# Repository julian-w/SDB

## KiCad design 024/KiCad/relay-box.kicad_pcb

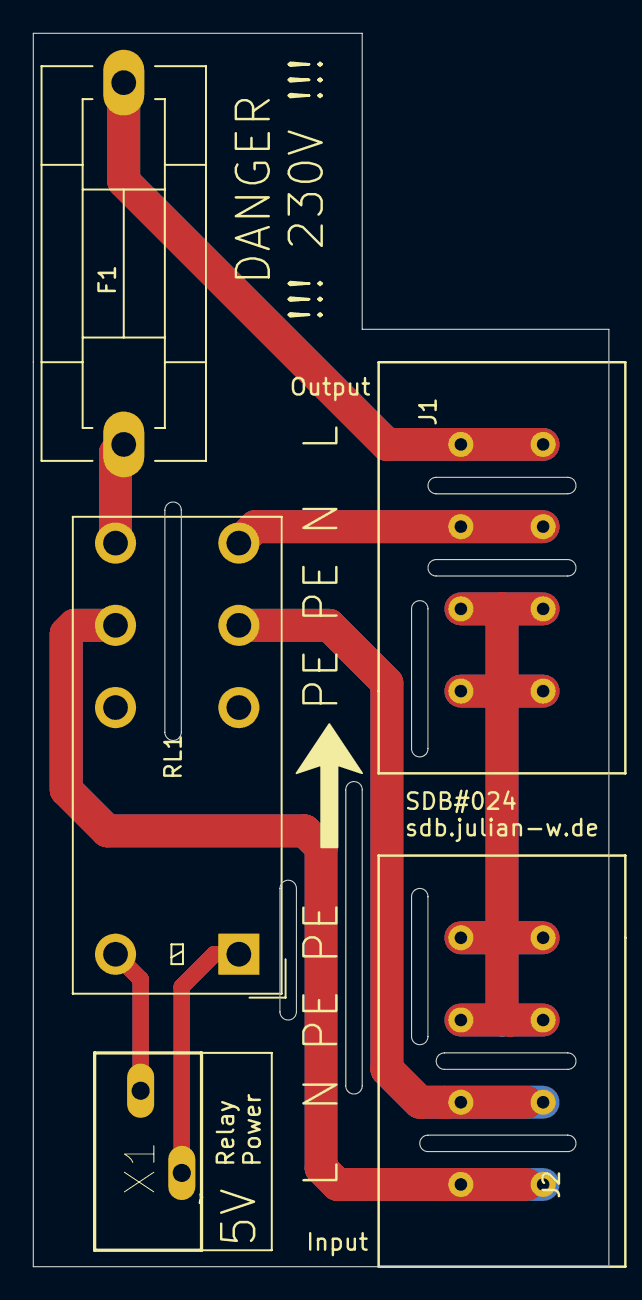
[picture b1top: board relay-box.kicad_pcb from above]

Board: 2 copper layers, 35.0 x 75.0 mm, 5 parts (0 on the bottom side), 8 nets.

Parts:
F1: Fuse; Fuseholder5x20_horiz_SemiClosed_Casing10x25mm
J1, J2: Conn_02x04_Row_Letter_Last; 5.00mm-4x2
RL1: G2RL-2-ASI-DC5; Relay_DPDT_Omron_G2RL
X1: 250-402_000-012; P-250-402

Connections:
unnamed: F1.1, RL1.5
unnamed: F1.2, J1.1a, J1.1b
unnamed: J1.2a, J1.2b, RL1.4
unnamed: J1.3a, J1.3b, J1.4a, J1.4b, J2.3a, J2.3b, J2.4a, J2.4b
unnamed: J2.1a, J2.1b, RL1.6
unnamed: J2.2a, J2.2b, RL1.3
unnamed: RL1.1, X1.L1
unnamed: RL1.8, X1.L2

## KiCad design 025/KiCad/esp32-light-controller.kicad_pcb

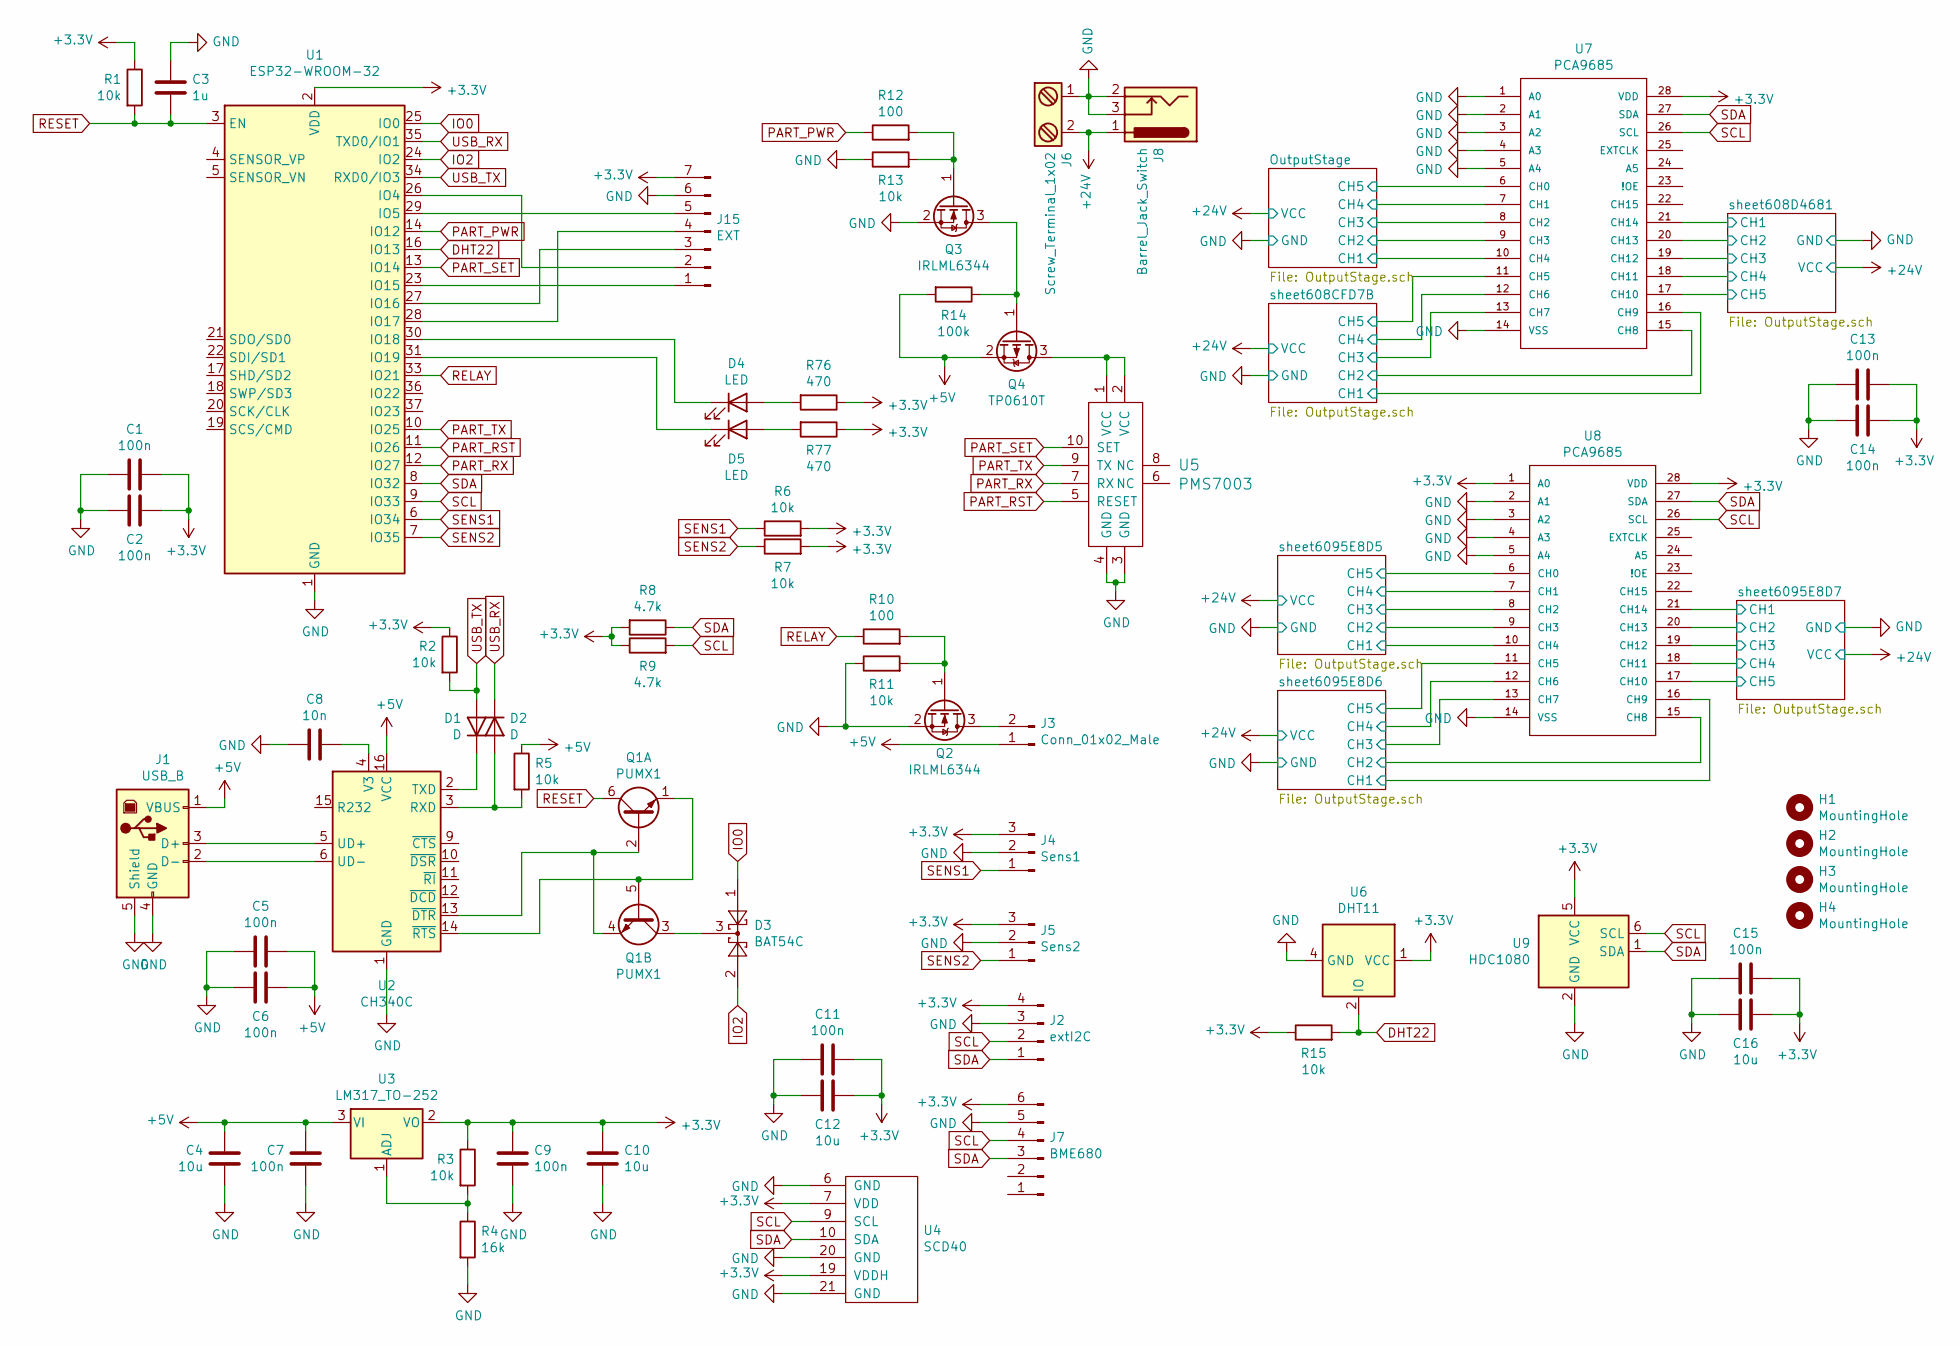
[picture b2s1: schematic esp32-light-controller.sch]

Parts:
C1, C2, C5, C6, C7, C9, C11, C13, C14, C15: 100n; C_0603
C3: 1u; C_0603
C4, C10, C12, C16: 10u; C_0603
C8: 10n; C_0603
D1, D2: D; D_SOD-123; LCSC C8598
D3: BAT54C; SOT-23
D4, D5: LED; LED_0603
H1, H2, H3, H4: MountingHole; MountingHole_3.2mm_M3
J1: USB_B; USB_B_Lumberg_2411_02_Horizontal
J2: extI2C; PinHeader_1x04_P2.54mm_Vertical
J3: Conn_01x02_Male; PinHeader_1x02_P2.54mm_Vertical
J4: Sens1; PinHeader_1x03_P2.54mm_Vertical
J5: Sens2; PinHeader_1x03_P2.54mm_Vertical
J6: Screw_Terminal_1x02; TE_826576-2_1x02_P3.96mm_Vertical
J7: BME680; PinHeader_1x06_P2.54mm_Vertical
J8: Barrel_Jack_Switch; BarrelJack_Horizontal
J15: EXT; PinHeader_1x07_P2.54mm_Vertical
Q1: PUMX1; SOT-363_SC-70-6
Q2, Q3: IRLML6344; SOT-23; LCSC C53550
Q4: TP0610T; SOT-23
R1, R2, R3, R5, R6, R7, R11, R13, R15: 10k; R_0603
R4: 16k; R_0603
R8, R9: 4.7k; R_0603
R10, R12: 100; R_0603
R14: 100k; R_0603
R76, R77: 470; R_0603
U1: ESP32-WROOM-32
U2: CH340C; SOIC-16_3.9x9.9mm_P1.27mm; LCSC C14267
U3: LM317_TO-252; TO-252-2; LCSC C75510
U4: SCD40; QFN-20_EP_10.1x10.1_Pitch1.25mm
U5: PMS7003
U6: DHT11; Aosong_DHT11_5.5x12.0_P2.54mm
U7, U8: PCA9685; SSOP-28_5.3x10.2mm_P0.65mm
U9: HDC1080; Texas_PWSON-N6; LCSC C82227

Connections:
+3V3: C1.1, C2.1, C9.1, C10.1, C11.1, C12.1, C13.1, C14.1, C15.1, C16.1, J2.4, J4.3, J5.3, J7.6, J15.7, R1.1, R2.1, R3.1, R6.2, R7.2, R8.2, R9.1, R15.1, R76.1, R77.1, U1.2 (VDD), U3.2 (VO), U4.7 (VDD), U4.19 (VDDH), U6.1 (VCC), U7.28 (VDD), U8.1 (A0), U8.28 (VDD), U9.5 (VCC)
+5V: C4.1, C5.1, C6.1, C7.1, J1.1 (VBUS), J3.1, Q4.2 (S), R5.1, R14.2, U2.16 (VCC), U3.3 (VI)
+24V: J6.2, J8.1; also elsewhere on the board
/OutputStage/CH1: U7.10 (CH4); also elsewhere on the board
/OutputStage/CH2: U7.9 (CH3); also elsewhere on the board
/OutputStage/CH3: U7.8 (CH2); also elsewhere on the board
/OutputStage/CH4: U7.7 (CH1); also elsewhere on the board
/OutputStage/CH5: U7.6 (CH0); also elsewhere on the board
/sheet608CFD7B/CH1: U7.16 (CH9); also elsewhere on the board
/sheet608CFD7B/CH2: U7.15 (CH8); also elsewhere on the board
/sheet608CFD7B/CH3: U7.13 (CH7); also elsewhere on the board
/sheet608CFD7B/CH4: U7.12 (CH6); also elsewhere on the board
/sheet608CFD7B/CH5: U7.11 (CH5); also elsewhere on the board
/sheet608D4681/CH1: U7.21 (CH14); also elsewhere on the board
/sheet608D4681/CH2: U7.20 (CH13); also elsewhere on the board
/sheet608D4681/CH3: U7.19 (CH12); also elsewhere on the board
/sheet608D4681/CH4: U7.18 (CH11); also elsewhere on the board
/sheet608D4681/CH5: U7.17 (CH10); also elsewhere on the board
/sheet6095E8D5/CH1: U8.10 (CH4); also elsewhere on the board
/sheet6095E8D5/CH2: U8.9 (CH3); also elsewhere on the board
/sheet6095E8D5/CH3: U8.8 (CH2); also elsewhere on the board
/sheet6095E8D5/CH4: U8.7 (CH1); also elsewhere on the board
/sheet6095E8D5/CH5: U8.6 (CH0); also elsewhere on the board
/sheet6095E8D6/CH1: U8.16 (CH9); also elsewhere on the board
/sheet6095E8D6/CH2: U8.15 (CH8); also elsewhere on the board
/sheet6095E8D6/CH3: U8.13 (CH7); also elsewhere on the board
/sheet6095E8D6/CH4: U8.12 (CH6); also elsewhere on the board
/sheet6095E8D6/CH5: U8.11 (CH5); also elsewhere on the board
/sheet6095E8D7/CH1: U8.21 (CH14); also elsewhere on the board
/sheet6095E8D7/CH2: U8.20 (CH13); also elsewhere on the board
/sheet6095E8D7/CH3: U8.19 (CH12); also elsewhere on the board
/sheet6095E8D7/CH4: U8.18 (CH11); also elsewhere on the board
/sheet6095E8D7/CH5: U8.17 (CH10); also elsewhere on the board
DHT22: R15.2, U1.16 (IO13), U6.2 (IO)
GND: C1.2, C2.2, C3.2, C4.2, C5.2, C6.2, C7.2, C8.2, C9.2, C10.2, C11.2, C12.2, C13.2, C14.2, C15.2, C16.2, J1.4 (GND), J1.5 (Shield), J2.3, J4.2, J5.2, J6.1, J7.5, J8.2, J8.3, J15.6, Q2.2 (S), Q3.2 (S), R4.2, R11.1, R13.1, U1.1 (GND), U1.15 (GND), U1.38 (GND), U1.39 (GND), U2.1 (GND), U4.6 (GND), U4.20 (GND), U4.21 (GND), U5.3 (GND), U5.4 (GND), U6.4 (GND), U7.1 (A0), U7.2 (A1), U7.3 (A2), U7.4 (A3), U7.5 (A4), U7.14 (VSS), U8.2 (A1), U8.3 (A2), U8.4 (A3), U8.5 (A4), U8.14 (VSS), U9.2 (GND); also elsewhere on the board
IO0: D3.1, U1.25 (IO0)
IO2: D3.2, U1.24 (IO2)
unnamed: C8.1, U2.4 (V3)
unnamed: D1.1 (K), U2.2 (TXD)
unnamed: D2.2 (A), R5.2, U2.3 (RXD)
unnamed: D3.3, Q1.3 (C2)
unnamed: D4.1 (K), U1.30 (IO18)
unnamed: D4.2 (A), R76.2
unnamed: D5.1 (K), U1.31 (IO19)
unnamed: D5.2 (A), R77.2
unnamed: J1.2 (D-), U2.6 (UD-)
unnamed: J1.3 (D+), U2.5 (UD+)
unnamed: J3.2, Q2.3 (D)
unnamed: J15.1, U1.23 (IO15)
unnamed: J15.2, U1.26 (IO4)
unnamed: J15.3, U1.27 (IO16)
unnamed: J15.4, U1.28 (IO17)
unnamed: J15.5, U1.29 (IO5)
unnamed: Q1.1 (E1), Q1.5 (B2), U2.14 (~RTS)
unnamed: Q1.2 (B1), Q1.4 (E2), U2.13 (~DTR)
unnamed: Q2.1 (G), R10.2, R11.2
unnamed: Q3.1 (G), R12.2, R13.2
unnamed: Q3.3 (D), Q4.1 (G), R14.1
unnamed: Q4.3 (D), U5.1 (VCC), U5.2 (VCC)
unnamed: R3.2, R4.1, U3.1 (ADJ)
PART_PWR: R12.1, U1.14 (IO12)
PART_RST: U1.11 (IO26), U5.5 (RESET)
PART_RX: U1.12 (IO27), U5.7 (RX)
PART_SET: U1.13 (IO14), U5.10 (SET)
PART_TX: U1.10 (IO25), U5.9 (TX)
RELAY: R10.1, U1.33 (IO21)
RESET: C3.1, Q1.6 (C1), R1.2, U1.3 (EN)
SCL: J2.2, J7.4, R9.2, U1.9 (IO33), U4.9 (SCL), U7.26 (SCL), U8.26 (SCL), U9.6 (SCL)
SDA: J2.1, J7.3, R8.1, U1.8 (IO32), U4.10 (SDA), U7.27 (SDA), U8.27 (SDA), U9.1 (SDA)
SENS1: J4.1, R6.1, U1.6 (IO34)
SENS2: J5.1, R7.1, U1.7 (IO35)
USB_RX: D2.1 (K), U1.35 (TXD0/IO1)
USB_TX: D1.2 (A), R2.2, U1.34 (RXD0/IO3)

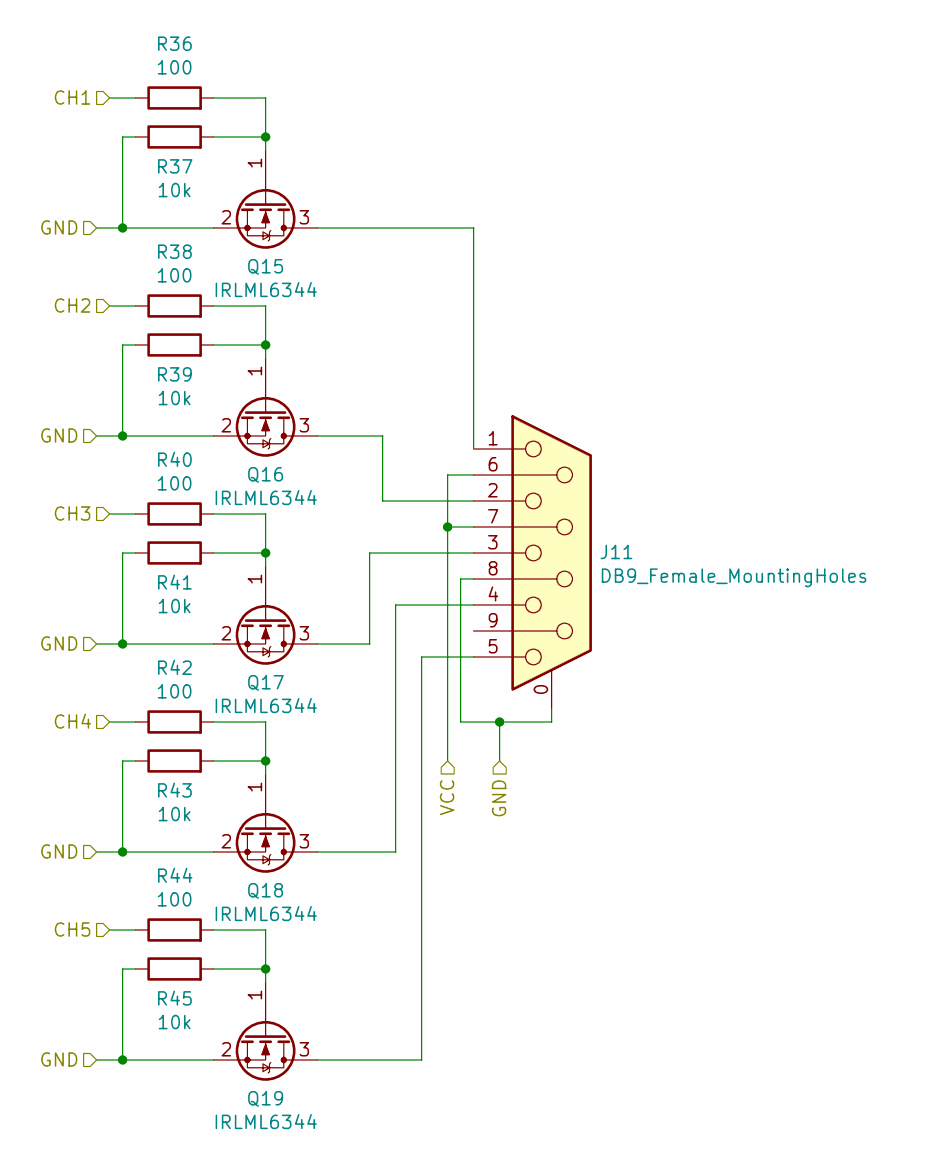
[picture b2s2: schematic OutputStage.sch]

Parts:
J9: DB9_Female_MountingHoles; DSUB-9_Female_Vertical_P2.77x2.84mm_MountingHoles; LCSC C86572
Q5, Q6, Q7, Q8, Q9: IRLML6344; SOT-23; LCSC C53550
R16, R18, R20, R22, R24: 100; R_0603
R17, R19, R21, R23, R25: 10k; R_0603

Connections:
+24V: J9.6, J9.7; also elsewhere on the board
/OutputStage/CH1: R16.1; also elsewhere on the board
/OutputStage/CH2: R18.1; also elsewhere on the board
/OutputStage/CH3: R20.1; also elsewhere on the board
/OutputStage/CH4: R22.1; also elsewhere on the board
/OutputStage/CH5: R24.1; also elsewhere on the board
GND: J9.0 (PAD), J9.8, Q5.2 (S), Q6.2 (S), Q7.2 (S), Q8.2 (S), Q9.2 (S), R17.1, R19.1, R21.1, R23.1, R25.1; also elsewhere on the board
unnamed: J9.1, Q5.3 (D)
unnamed: J9.2, Q6.3 (D)
unnamed: J9.3, Q7.3 (D)
unnamed: J9.4, Q8.3 (D)
unnamed: J9.5, Q9.3 (D)
unnamed: Q5.1 (G), R16.2, R17.2
unnamed: Q6.1 (G), R18.2, R19.2
unnamed: Q7.1 (G), R20.2, R21.2
unnamed: Q8.1 (G), R22.2, R23.2
unnamed: Q9.1 (G), R24.2, R25.2

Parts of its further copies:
J10, J11, J12, J13, J14: DB9_Female_MountingHoles; DSUB-9_Female_Vertical_P2.77x2.84mm_MountingHoles; LCSC C86572
Q10, Q11, Q12, Q13, Q14, Q15, Q16, Q17, Q18, Q19, Q20, Q21, Q22, Q23, Q24, Q25, Q26, Q27, Q28, Q29, Q30, Q31, Q32, Q33, Q34: IRLML6344; SOT-23; LCSC C53550
R26, R28, R30, R32, R34, R36, R38, R40, R42, R44, R46, R48, R50, R52, R54, R56, R58, R60, R62, R64, R66, R68, R70, R72, R74: 100; R_0603
R27, R29, R31, R33, R35, R37, R39, R41, R43, R45, R47, R49, R51, R53, R55, R57, R59, R61, R63, R65, R67, R69, R71, R73, R75: 10k; R_0603

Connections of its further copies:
+24V: J10.6, J10.7, J11.6, J11.7, J12.6, J12.7, J13.6, J13.7, J14.6, J14.7; also elsewhere on the board
/sheet608CFD7B/CH1: R26.1; also elsewhere on the board
/sheet608CFD7B/CH2: R28.1; also elsewhere on the board
/sheet608CFD7B/CH3: R30.1; also elsewhere on the board
/sheet608CFD7B/CH4: R32.1; also elsewhere on the board
/sheet608CFD7B/CH5: R34.1; also elsewhere on the board
/sheet608D4681/CH1: R36.1; also elsewhere on the board
/sheet608D4681/CH2: R38.1; also elsewhere on the board
/sheet608D4681/CH3: R40.1; also elsewhere on the board
/sheet608D4681/CH4: R42.1; also elsewhere on the board
/sheet608D4681/CH5: R44.1; also elsewhere on the board
/sheet6095E8D5/CH1: R46.1; also elsewhere on the board
/sheet6095E8D5/CH2: R48.1; also elsewhere on the board
/sheet6095E8D5/CH3: R50.1; also elsewhere on the board
/sheet6095E8D5/CH4: R52.1; also elsewhere on the board
/sheet6095E8D5/CH5: R54.1; also elsewhere on the board
/sheet6095E8D6/CH1: R56.1; also elsewhere on the board
/sheet6095E8D6/CH2: R58.1; also elsewhere on the board
/sheet6095E8D6/CH3: R60.1; also elsewhere on the board
/sheet6095E8D6/CH4: R62.1; also elsewhere on the board
/sheet6095E8D6/CH5: R64.1; also elsewhere on the board
/sheet6095E8D7/CH1: R66.1; also elsewhere on the board
/sheet6095E8D7/CH2: R68.1; also elsewhere on the board
/sheet6095E8D7/CH3: R70.1; also elsewhere on the board
/sheet6095E8D7/CH4: R72.1; also elsewhere on the board
/sheet6095E8D7/CH5: R74.1; also elsewhere on the board
GND: J10.0 (PAD), J10.8, J11.0 (PAD), J11.8, J12.0 (PAD), J12.8, J13.0 (PAD), J13.8, J14.0 (PAD), J14.8, Q10.2 (S), Q11.2 (S), Q12.2 (S), Q13.2 (S), Q14.2 (S), Q15.2 (S), Q16.2 (S), Q17.2 (S), Q18.2 (S), Q19.2 (S), Q20.2 (S), Q21.2 (S), Q22.2 (S), Q23.2 (S), Q24.2 (S), Q25.2 (S), Q26.2 (S), Q27.2 (S), Q28.2 (S), Q29.2 (S), Q30.2 (S), Q31.2 (S), Q32.2 (S), Q33.2 (S), Q34.2 (S), R27.1, R29.1, R31.1, R33.1, R35.1, R37.1, R39.1, R41.1, R43.1, R45.1, R47.1, R49.1, R51.1, R53.1, R55.1, R57.1, R59.1, R61.1, R63.1, R65.1, R67.1, R69.1, R71.1, R73.1, R75.1; also elsewhere on the board
unnamed: J10.1, Q10.3 (D)
unnamed: J10.2, Q11.3 (D)
unnamed: J10.3, Q12.3 (D)
unnamed: J10.4, Q13.3 (D)
unnamed: J10.5, Q14.3 (D)
unnamed: J11.1, Q15.3 (D)
unnamed: J11.2, Q16.3 (D)
unnamed: J11.3, Q17.3 (D)
unnamed: J11.4, Q18.3 (D)
unnamed: J11.5, Q19.3 (D)
unnamed: J12.1, Q20.3 (D)
unnamed: J12.2, Q21.3 (D)
unnamed: J12.3, Q22.3 (D)
unnamed: J12.4, Q23.3 (D)
unnamed: J12.5, Q24.3 (D)
unnamed: J13.1, Q25.3 (D)
unnamed: J13.2, Q26.3 (D)
unnamed: J13.3, Q27.3 (D)
unnamed: J13.4, Q28.3 (D)
unnamed: J13.5, Q29.3 (D)
unnamed: J14.1, Q30.3 (D)
unnamed: J14.2, Q31.3 (D)
unnamed: J14.3, Q32.3 (D)
unnamed: J14.4, Q33.3 (D)
unnamed: J14.5, Q34.3 (D)
unnamed: Q10.1 (G), R26.2, R27.2
unnamed: Q11.1 (G), R28.2, R29.2
unnamed: Q12.1 (G), R30.2, R31.2
unnamed: Q13.1 (G), R32.2, R33.2
unnamed: Q14.1 (G), R34.2, R35.2
unnamed: Q15.1 (G), R36.2, R37.2
unnamed: Q16.1 (G), R38.2, R39.2
unnamed: Q17.1 (G), R40.2, R41.2
unnamed: Q18.1 (G), R42.2, R43.2
unnamed: Q19.1 (G), R44.2, R45.2
unnamed: Q20.1 (G), R46.2, R47.2
unnamed: Q21.1 (G), R48.2, R49.2
unnamed: Q22.1 (G), R50.2, R51.2
unnamed: Q23.1 (G), R52.2, R53.2
unnamed: Q24.1 (G), R54.2, R55.2
unnamed: Q25.1 (G), R56.2, R57.2
unnamed: Q26.1 (G), R58.2, R59.2
unnamed: Q27.1 (G), R60.2, R61.2
unnamed: Q28.1 (G), R62.2, R63.2
unnamed: Q29.1 (G), R64.2, R65.2
unnamed: Q30.1 (G), R66.2, R67.2
unnamed: Q31.1 (G), R68.2, R69.2
unnamed: Q32.1 (G), R70.2, R71.2
unnamed: Q33.1 (G), R72.2, R73.2
unnamed: Q34.1 (G), R74.2, R75.2

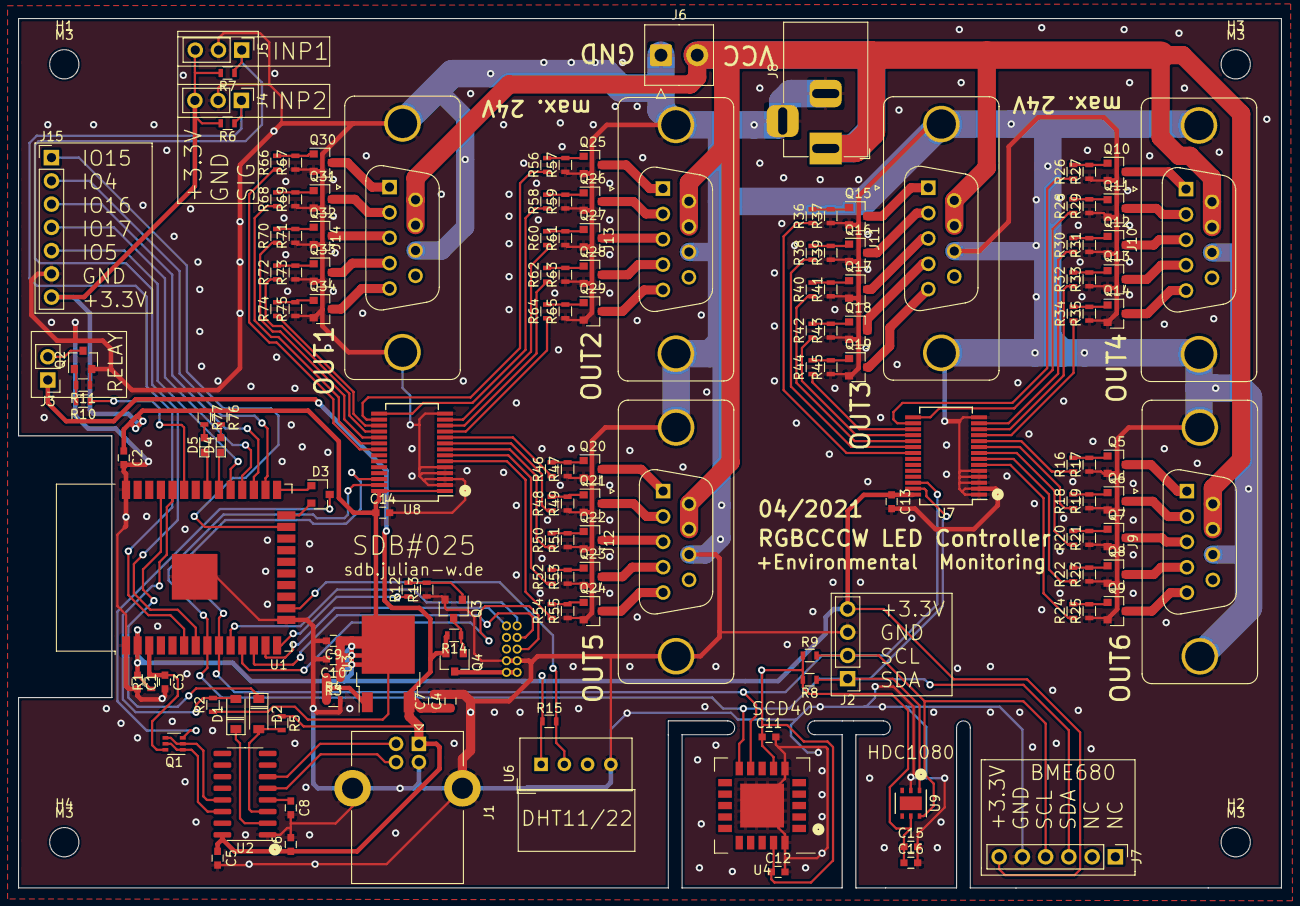
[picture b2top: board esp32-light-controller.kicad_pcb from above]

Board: 2 copper layers, 138.0 x 95.0 mm, 160 parts (1 on the bottom side), 133 nets.

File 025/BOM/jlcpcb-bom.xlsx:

Column1 | Column2 | Column3 | Column4
Comment | Designator | Footprint | LCSC
100n | C1,C2,C5,C6,C7,C9,C11,C13,C14,C15 | Capacitors_SMD:C_0603 | C14663
10u | C4,C10,C12,C16 | Capacitors_SMD:C_0603 | C19702
1u | C3 | Capacitors_SMD:C_0603 | C15849
10n | C8 | Capacitors_SMD:C_0603 | C57112
D | D1,D2 | Diodes_SMD:D_SOD-123 | C8598
BAT54C | D3 | Package_TO_SOT_SMD:SOT-23 | C14308
LED | D4 | LEDs:LED_0603 | C72043
LED | D5 | LEDs:LED_0603 | C72038
MountingHole | H1,H2,H3,H4 | Mounting_Holes:MountingHole_3.2mm_M3
USB_B | J1 | Connector_USB:USB_B_Lumberg_2411_02_Horizontal
EXT | J15 | Connector_PinHeader_2.54mm:PinHeader_1x07_P2.54mm_Vertical
extI2C | J2 | Connector_PinHeader_2.54mm:PinHeader_1x04_P2.54mm_Vertical
Conn_01x02_Male | J3 | Connector_PinHeader_2.54mm:PinHeader_1x02_P2.54mm_Vertical
Sens1 | J4 | Connector_PinHeader_2.54mm:PinHeader_1x03_P2.54mm_Vertical
Sens2 | J5 | Connector_PinHeader_2.54mm:PinHeader_1x03_P2.54mm_Vertical
Screw_Terminal_1x02 | J6 | Connector_TE-Connectivity:TE_826576-2_1x02_P3.96mm_Vertical
BME680 | J7 | Connector_PinHeader_2.54mm:PinHeader_1x06_P2.54mm_Vertical
Barrel_Jack_Switch | J8 | Connector_BarrelJack:BarrelJack_Horizontal
DB9_Female_MountingHoles | J9,J10,J11,J12,J13,J14 | Connector_Dsub:DSUB-9_Female_Vertical_P2.77x2.84mm_MountingHoles | C86572
PUMX1 | Q1 | Package_TO_SOT_SMD:SOT-363_SC-70-6 | C79972
IRLML6344 | Q2,Q3,Q5,Q6,Q7,Q8,Q9,Q10,Q11,Q12,Q13,Q14,Q15,Q16,Q17,Q18,Q19,Q20,Q21,Q22,Q23,Q2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 | Package_TO_SOT_SMD:SOT-23 | C53550
TP0610T | Q4 | Package_TO_SOT_SMD:SOT-23 | C10487
100 | R10,R12,R16,R18,R20,R22,R24,R26,R28,R30,R32,R34,R36,R38,R40,R42,R44,R46,R48,R50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 | Resistors_SMD:R_0603 | C22775
100k | R14 | Resistors_SMD:R_0603 | C25803
10k | R1,R2,R3,R5,R6,R7,R11,R13,R15,R17,R19,R21,R23,R25,R27,R29,R31,R33,R35,R37,R39,R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 | Resistors_SMD:R_0603 | C25804
16k | R4 | Resistors_SMD:R_0603 | C22818
470 | R76,R77 | Resistors_SMD:R_0603 | C23179
4.7k | R8,R9 | Resistors_SMD:R_0603 | C23162
ESP32-WROOM-32 | U1 | RF_Module:ESP32-WROOM-32 | C473012
CH340C | U2 | Package_SO:SOIC-16_3.9x9.9mm_P1.27mm | C14267
LM317_TO-252 | U3 | Package_TO_SOT_SMD:TO-252-2 | C75510
SCD40 | U4 | 009162006301150:QFN-20_EP_10.1x10.1_Pitch1.25mm
PMS7003 | U5 | Sensors_Detectors:PMS7003
DHT11 | U6 | Sensor:Aosong_DHT11_5.5x12.0_P2.54mm
PCA9685 | U7,U8 | Package_SO:SSOP-28_5.3x10.2mm_P0.65mm | C92206
HDC1080 | U9 | Package_SON:Texas_PWSON-N6 | C82227

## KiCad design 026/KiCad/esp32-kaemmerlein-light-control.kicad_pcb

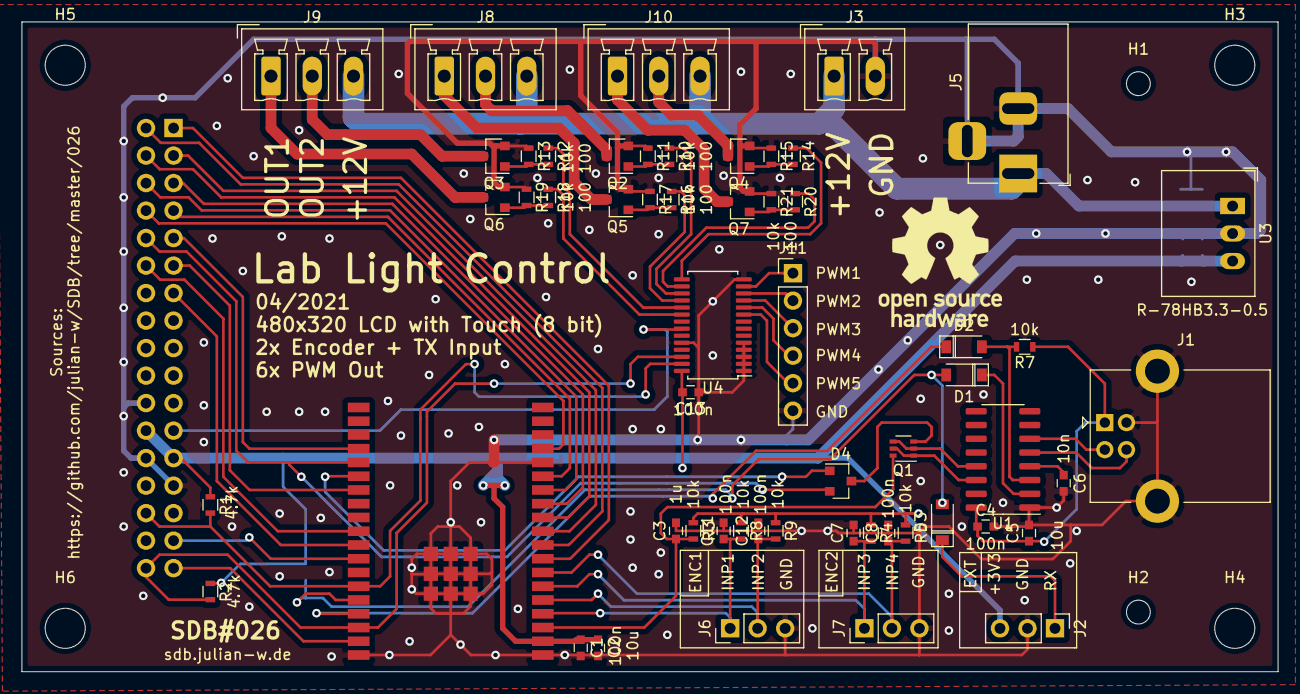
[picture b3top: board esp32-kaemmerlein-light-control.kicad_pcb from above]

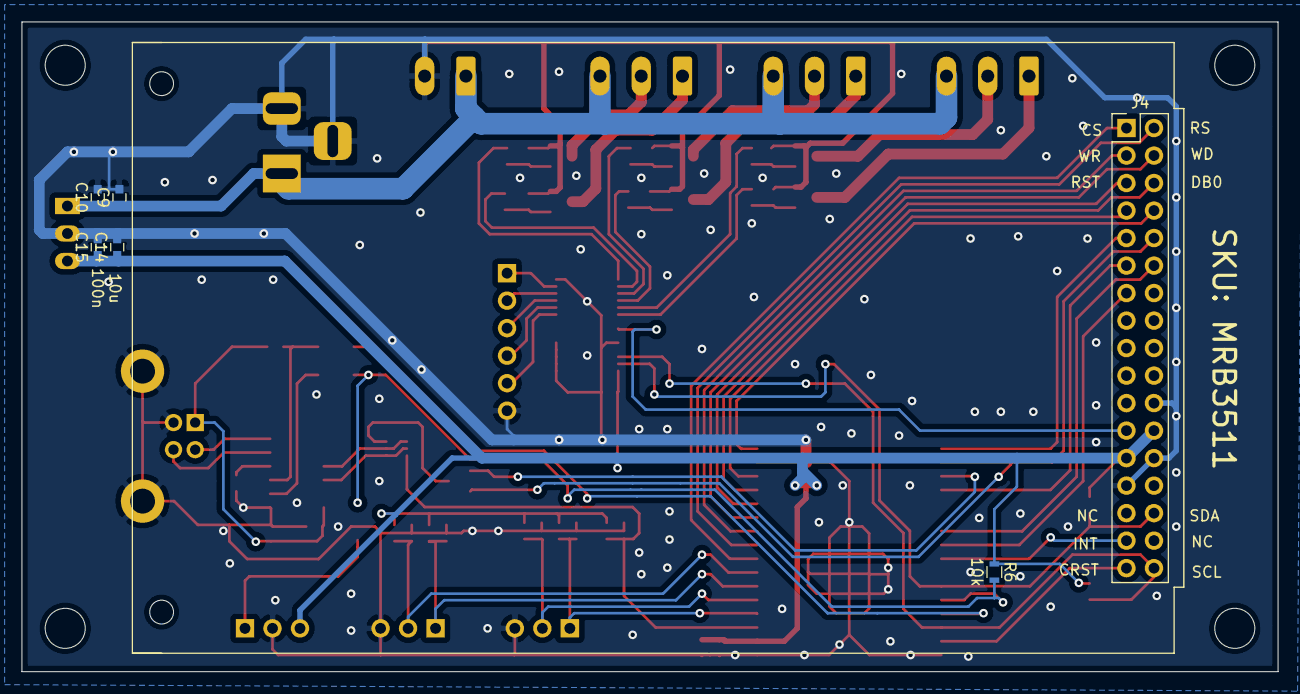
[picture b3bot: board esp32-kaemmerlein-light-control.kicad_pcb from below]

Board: 2 copper layers, 116.0 x 60.0 mm, 69 parts (6 on the bottom side), 62 nets.

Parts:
C1, C2, C4, C5, C7, C8, C10, C11, C12, C13, C15: 100n; C_0603
C3: 1u; C_0603
C6: 10n; C_0603
C9, C14: 10u; C_0603
D1, D2, D3: D; D_SOD-123
D4: BAT54C; SOT-23
H1, H2: MountingHole; MountingHole_2.2mm_M2
H3, H4, H5, H6: MountingHole; MountingHole_3.7mm
J1: USB_B; USB_B_Lumberg_2411_02_Horizontal
J2: EXT; PinHeader_1x03_P2.54mm_Vertical
J3: LED_PWR; PhoenixContact_MCV_1,5_2-G-3.81_1x02_P3.81mm_Vertical
J4: 3.5 Inch Display; PinHeader_2x17_P2.54mm_Vertical
J5: Barrel_Jack_Switch; BarrelJack_Horizontal
J6: ENC1; PinHeader_1x03_P2.54mm_Vertical
J7: ENC2; PinHeader_1x03_P2.54mm_Vertical
J8, J9, J10: Conn_01x03; PhoenixContact_MCV_1,5_3-G-3.81_1x03_P3.81mm_Vertical
J11: Conn_01x06_Male; PinHeader_1x06_P2.54mm_Vertical
LOGO1: Logo_Open_Hardware_Small; OSHW-Logo_11.4x12mm_SilkScreen
Q1: PUMX1; SOT-363_SC-70-6
Q2, Q3, Q4, Q5, Q6, Q7: IRLML6344; SOT-23
R1, R2: 4.7k; R_0603
R3, R4, R5, R6, R7, R8, R9, R11, R13, R15, R17, R19, R21: 10k; R_0603
R10, R12, R14, R16, R18, R20: 100; R_0603
U1: CH340C; SOIC-16_3.9x9.9mm_P1.27mm
U2: ESP32-WROVER-E
U3: R-78HB3.3-0.5; Converter_DCDC_RECOM_R-78HB-0.5_THT
U4: PCA9685PW; TSSOP-28_4.4x9.7mm_P0.65mm

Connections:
+3V3: C1.1, C2.1, C13.2, C14.1, C15.1, J2.3, J4.24, J4.25, R1.1, R2.1, R3.1, R4.1, R5.1, R6.1, R8.1, R9.1, U2.2, U3.3, U4.28
+5V: C4.1, C5.1, J1.1, R7.1, U1.16
+12V: C9.1, C10.1, J3.1, J5.1, J8.3, J9.3, J10.3, U3.1
BL: J4.23, U4.22
CRST: J4.33, U2.37
CS: J4.1, U2.8
DB0: J4.6, U2.13
DB1: J4.7, U2.14
DB2: J4.8, U2.16
DB3: J4.9, U2.23
DB4: D4.2, J4.10, U2.24
DB5: J4.11, U2.26
DB6: J4.12, U2.29
DB7: J4.13, U2.30
GND: C1.2, C2.2, C3.2, C4.2, C5.2, C6.2, C7.2, C8.2, C9.2, C10.2, C11.2, C12.2, C13.1, C14.2, C15.2, J1.4, J1.5, J2.2, J3.2, J4.22, J4.26, J4.27, J5.2, J5.3, J6.3, J7.3, J11.6, Q2.2, Q3.2, Q4.2, Q5.2, Q6.2, Q7.2, R11.1, R13.1, R15.1, R17.1, R19.1, R21.1, U1.1, U2.1, U2.15, U2.38, U2.39, U3.2, U4.1, U4.2, U4.3, U4.4, U4.5, U4.14, U4.24
INT: J4.31, U2.31
IO0: D4.1, U2.25
IO34: C7.1, J7.1, R4.2, U2.6
IO35: C8.1, J7.2, R5.2, U2.7
IO36: C11.1, J6.1, R8.2, U2.4
IO39: C12.1, J6.2, R9.2, U2.5
LED1: R10.1, U4.17
LED2: R16.1, U4.18
LED3: R12.1, U4.19
LED4: R18.1, U4.20
LED5: R14.1, U4.15
LED6: R20.1, U4.16
unnamed: C6.1, U1.4
unnamed: D1.1, U1.2
unnamed: D2.2, R7.2, U1.3
unnamed: D3.1, J2.1
unnamed: D4.3, Q1.3
unnamed: J1.2, U1.6
unnamed: J1.3, U1.5
unnamed: J8.1, Q5.3
unnamed: J8.2, Q2.3
unnamed: J9.1, Q6.3
unnamed: J9.2, Q3.3
unnamed: J10.1, Q7.3
unnamed: J10.2, Q4.3
unnamed: J11.1, U4.13
unnamed: J11.2, U4.12
unnamed: J11.3, U4.11
unnamed: J11.4, U4.10
unnamed: J11.5, U4.9
unnamed: Q1.1, Q1.5, U1.14
unnamed: Q1.2, Q1.4, U1.13
unnamed: Q2.1, R10.2, R11.2
unnamed: Q3.1, R12.2, R13.2
unnamed: Q4.1, R14.2, R15.2
unnamed: Q5.1, R16.2, R17.2
unnamed: Q6.1, R18.2, R19.2
unnamed: Q7.1, R20.2, R21.2
RESET: C3.1, Q1.6, R3.2, U2.3
RS: J4.2, U2.9
RST: J4.5, U2.12
SCL: J4.34, R2.2, U2.36, U4.26
SDA: J4.30, R1.2, U2.33, U4.27
USB_RX: D2.1, U2.35
USB_TX: D1.2, D3.2, R6.2, U2.34
WD: J4.4, U2.11
WR: J4.3, U2.10
